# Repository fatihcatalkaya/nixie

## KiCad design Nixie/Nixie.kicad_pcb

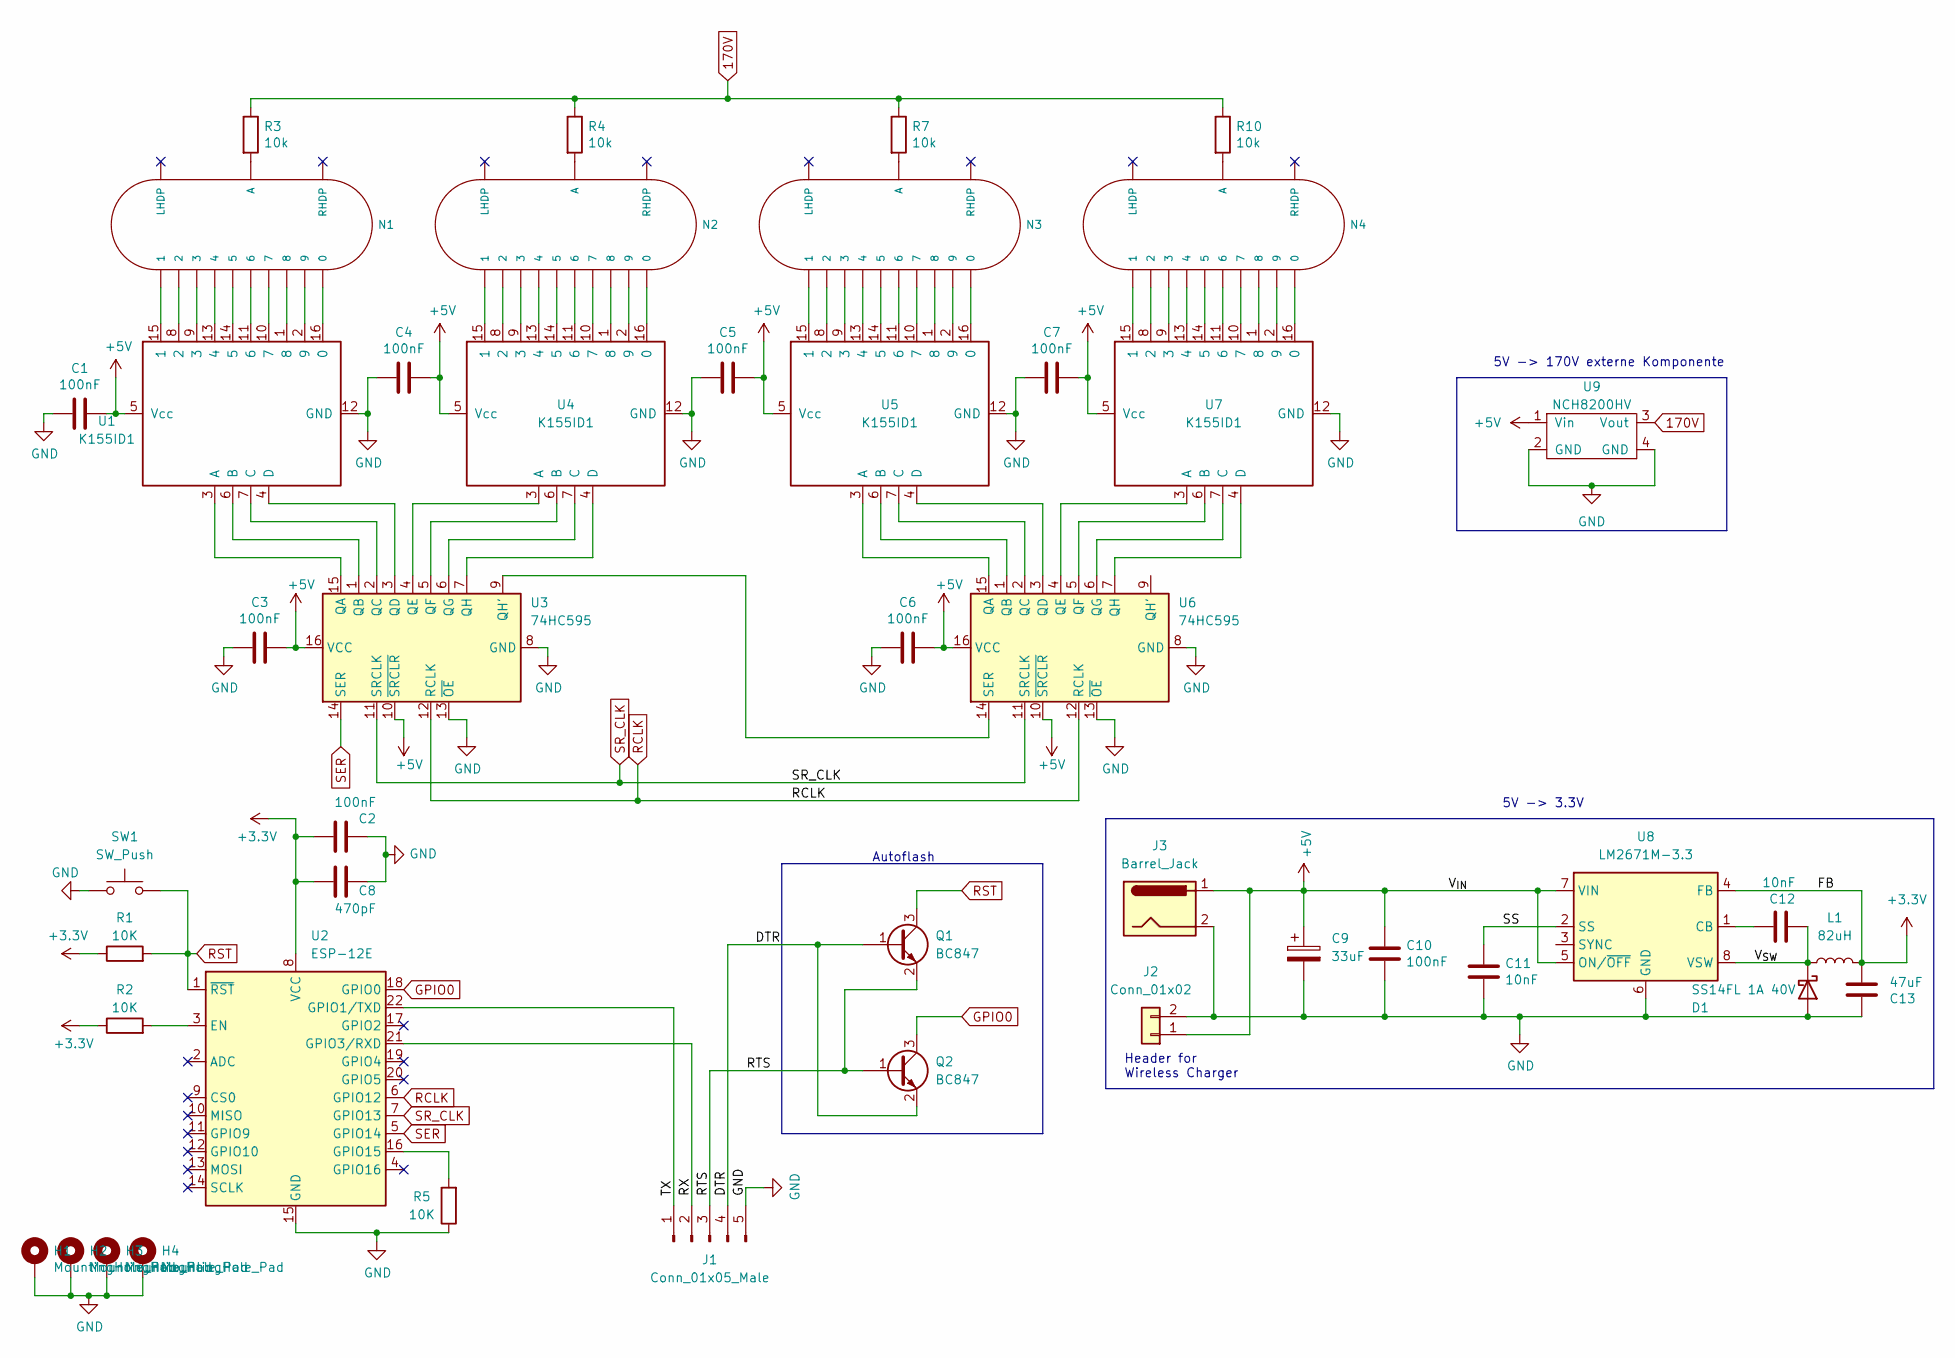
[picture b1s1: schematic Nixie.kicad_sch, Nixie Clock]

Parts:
C1, C2, C3, C4, C5, C6, C7: 100nF; C_0603_1608Metric_Pad1.08x0.95mm_HandSolder; LCSC C14663
C8: 470pF; C_0603_1608Metric_Pad1.08x0.95mm_HandSolder; LCSC C1620
C9: 33uF; CP_Elec_4x4.5
C10: 100nF; C_0603_1608Metric; LCSC C14663
C11, C12: 10nF; C_0603_1608Metric; LCSC C57112
C13: 47uF; C_0603_1608Metric
D1: SS14FL 1A 40V; D_SMA; LCSC C2480
H1, H2, H3, H4: MountingHole_Pad; MountingHole_3.2mm_M3_Pad
J1: Conn_01x05_Male; PinHeader_1x05_P2.54mm_Vertical
J2: Conn_01x02; JST_EH_B2B-EH-A_1x02_P2.50mm_Vertical
J3: Barrel_Jack; BarrelJack_Horizontal
L1: 82uH; L_1210_3225Metric
N1, N2, N3, N4: IN-16; russian-nixies-IN-16
Q1, Q2: BC847; SOT-23
R1, R2, R5: 10K; R_0603_1608Metric_Pad0.98x0.95mm_HandSolder; LCSC C25804
R3, R4, R7, R10: 10k; R_0603_1608Metric_Pad0.98x0.95mm_HandSolder; LCSC C25804
SW1: SW_Push; SW_Push_1P1T_NO_CK_KSC7xxJ
U1, U4, U5, U7: K155ID1; DIP-16_W7.62mm_Socket
U2: ESP-12E
U3, U6: 74HC595; SOIC-16_3.9x9.9mm_P1.27mm; LCSC C5947
U8: LM2671M-3.3; SOIC-8_3.9x4.9mm_P1.27mm
U9: NCH8200HV

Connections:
170V: R3.1, R4.1, R7.1, R10.1, U9.3 (Vout)
+3.3V: C2.1, C8.1, C13.1, L1.2, R1.1, R2.1, U2.8 (VCC), U8.4 (FB); also elsewhere on the board
+5V: C1.1, C3.1, C4.1, C5.1, C6.1, C7.1, C9.1, C10.1, J2.1, J3.1, U1.5 (Vcc), U3.10 (~SRCLR), U3.16 (VCC), U4.5 (Vcc), U5.5 (Vcc), U6.10 (~SRCLR), U6.16 (VCC), U7.5 (Vcc), U8.5 (ON/~OFF), U8.7 (VIN), U9.1 (Vin); also elsewhere on the board
/DTR: J1.4, Q1.1 (B), Q2.2 (E)
/RTS: J1.3, Q1.2 (E), Q2.1 (B)
/RX: J1.2, U2.21 (GPIO3/RXD)
/SS: C11.1, U8.2 (SS)
/TX: J1.1, U2.22 (GPIO1/TXD)
/V_{SW}: C12.2, D1.1 (K), L1.1, U8.8 (VSW)
GND: C1.2, C2.2, C3.2, C4.2, C5.2, C6.2, C7.2, C8.2, C9.2, C10.2, C11.2, C13.2, D1.2 (A), H1.1, H2.1, H3.1, H4.1, J1.5, J2.2, J3.2, R5.1, SW1.1, U1.12 (GND), U2.15 (GND), U3.8 (GND), U3.13 (~OE), U4.12 (GND), U5.12 (GND), U6.8 (GND), U6.13 (~OE), U7.12 (GND), U8.6 (GND), U9.2 (GND), U9.4 (GND); also elsewhere on the board
GPIO0: Q2.3 (C), U2.18 (GPIO0)
unnamed: C12.1, U8.1 (CB)
unnamed: N1.0, U1.16 (0)
unnamed: N1.1, U1.15 (1)
unnamed: N1.2, U1.8 (2)
unnamed: N1.3, U1.9 (3)
unnamed: N1.4, U1.13 (4)
unnamed: N1.5, U1.14 (5)
unnamed: N1.6, U1.11 (6)
unnamed: N1.7, U1.10 (7)
unnamed: N1.8, U1.1 (8)
unnamed: N1.9, U1.2 (9)
unnamed: N1.A, R3.2
unnamed: N2.0, U4.16 (0)
unnamed: N2.1, U4.15 (1)
unnamed: N2.2, U4.8 (2)
unnamed: N2.3, U4.9 (3)
unnamed: N2.4, U4.13 (4)
unnamed: N2.5, U4.14 (5)
unnamed: N2.6, U4.11 (6)
unnamed: N2.7, U4.10 (7)
unnamed: N2.8, U4.1 (8)
unnamed: N2.9, U4.2 (9)
unnamed: N2.A, R4.2
unnamed: N3.0, U5.16 (0)
unnamed: N3.1, U5.15 (1)
unnamed: N3.2, U5.8 (2)
unnamed: N3.3, U5.9 (3)
unnamed: N3.4, U5.13 (4)
unnamed: N3.5, U5.14 (5)
unnamed: N3.6, U5.11 (6)
unnamed: N3.7, U5.10 (7)
unnamed: N3.8, U5.1 (8)
unnamed: N3.9, U5.2 (9)
unnamed: N3.A, R7.2
unnamed: N4.0, U7.16 (0)
unnamed: N4.1, U7.15 (1)
unnamed: N4.2, U7.8 (2)
unnamed: N4.3, U7.9 (3)
unnamed: N4.4, U7.13 (4)
unnamed: N4.5, U7.14 (5)
unnamed: N4.6, U7.11 (6)
unnamed: N4.7, U7.10 (7)
unnamed: N4.8, U7.1 (8)
unnamed: N4.9, U7.2 (9)
unnamed: N4.A, R10.2
unnamed: R2.2, U2.3 (EN)
unnamed: R5.2, U2.16 (GPIO15)
unnamed: U1.3 (A), U3.15 (QA)
unnamed: U1.4 (D), U3.3 (QD)
unnamed: U1.6 (B), U3.1 (QB)
unnamed: U1.7 (C), U3.2 (QC)
unnamed: U3.4 (QE), U4.3 (A)
unnamed: U3.5 (QF), U4.6 (B)
unnamed: U3.6 (QG), U4.7 (C)
unnamed: U3.7 (QH), U4.4 (D)
unnamed: U3.9 (QH'), U6.14 (SER)
unnamed: U5.3 (A), U6.15 (QA)
unnamed: U5.4 (D), U6.3 (QD)
unnamed: U5.6 (B), U6.1 (QB)
unnamed: U5.7 (C), U6.2 (QC)
unnamed: U6.4 (QE), U7.3 (A)
unnamed: U6.5 (QF), U7.6 (B)
unnamed: U6.6 (QG), U7.7 (C)
unnamed: U6.7 (QH), U7.4 (D)
RCLK: U2.6 (GPIO12), U3.12 (RCLK), U6.12 (RCLK)
RST: Q1.3 (C), R1.2, SW1.2, U2.1 (~RST)
SER: U2.5 (GPIO14), U3.14 (SER)
SR_CLK: U2.7 (GPIO13), U3.11 (SRCLK), U6.11 (SRCLK)

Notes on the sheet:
5V -> 3.3V
Autoflash
5V -> 170V externe Komponente
Header for Wireless Charger

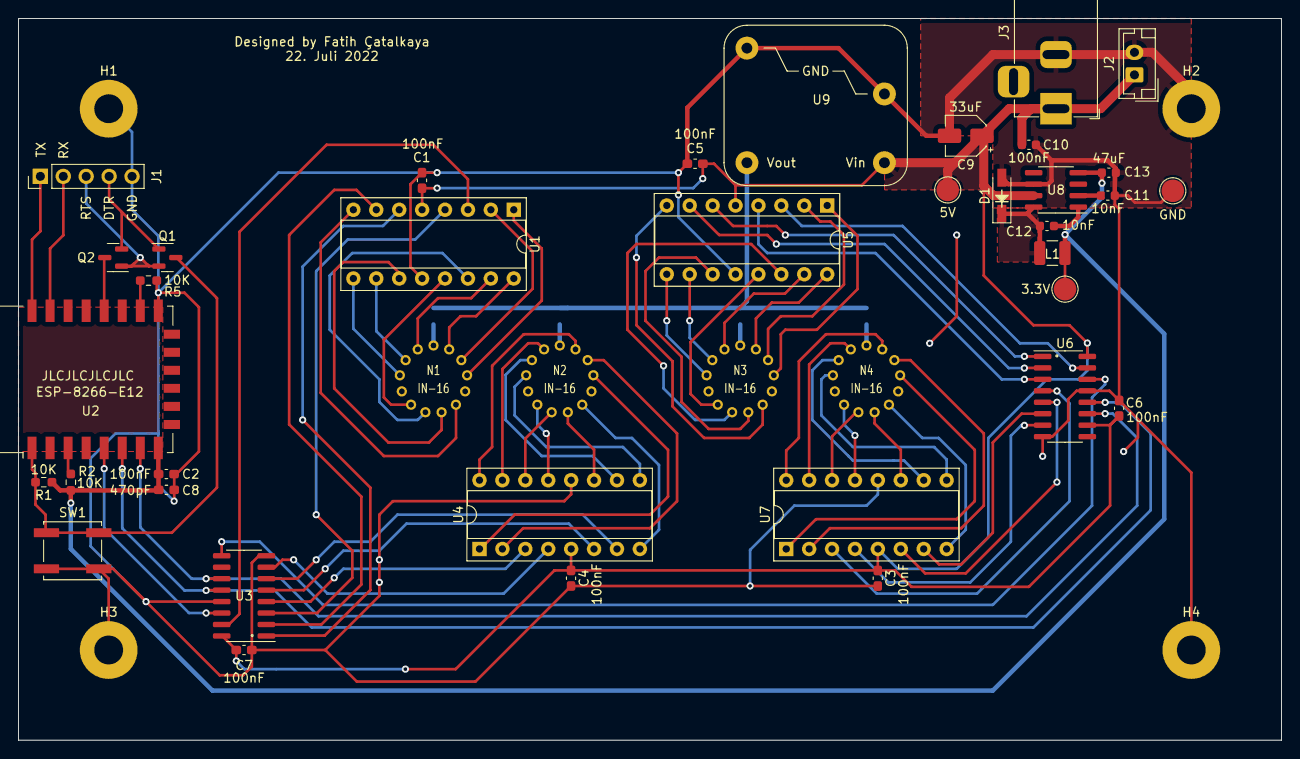
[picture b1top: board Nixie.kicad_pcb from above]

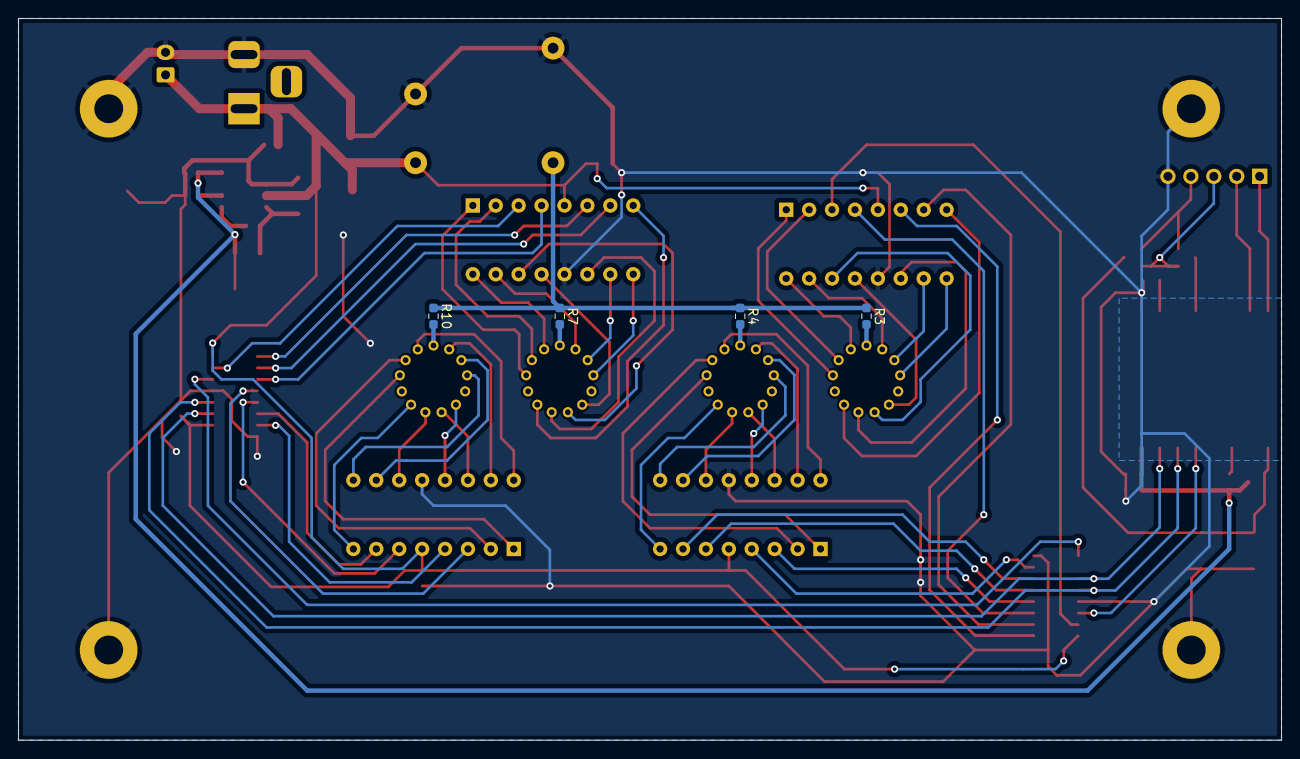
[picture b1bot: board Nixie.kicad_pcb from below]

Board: 2 copper layers, 140.0 x 80.0 mm, 48 parts (4 on the bottom side), 79 nets.

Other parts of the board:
3.3V, 5V: TestPoint_Pad_D2.5mm
GND: TestPoint_Pad_D2.5mm

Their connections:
+3.3V: 3.3V.1; also elsewhere on the board
+5V: 5V.1; also elsewhere on the board
GND: GND.1; also elsewhere on the board

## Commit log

2021-03-21 Created K155ID1 Library and created basic layout
2021-03-29 5V -> 3.3V hinzugefügt
2021-03-29 USB Header hinzugefügt
2021-03-30 5v to 170v Step Up hinzugefügt
2021-04-03 Werte angeglichen
2021-04-03 Added BOM
2021-09-05 Kleinere Anpassungen
2022-07-10 Kleinere Änderungen an der Beschaltung des ESP8266
2022-07-10 Reset Knopf hinzugefügt
2022-07-10 Platine begonnen
2022-07-11 Platinenlayout begonnen
2022-07-12 Added missing footprints to project
2022-07-12 PCB fertiggestellt
2022-07-12 Added solid ground planes
2022-07-16 Designed 2-layer PCB
2022-07-16 Smaller Adjustments
2022-07-21 Platine neu gezeichnet mit gmit genauen Maßen
2022-07-21 Small adjustments
2022-07-22 Kleine verschiedene Änderungen
